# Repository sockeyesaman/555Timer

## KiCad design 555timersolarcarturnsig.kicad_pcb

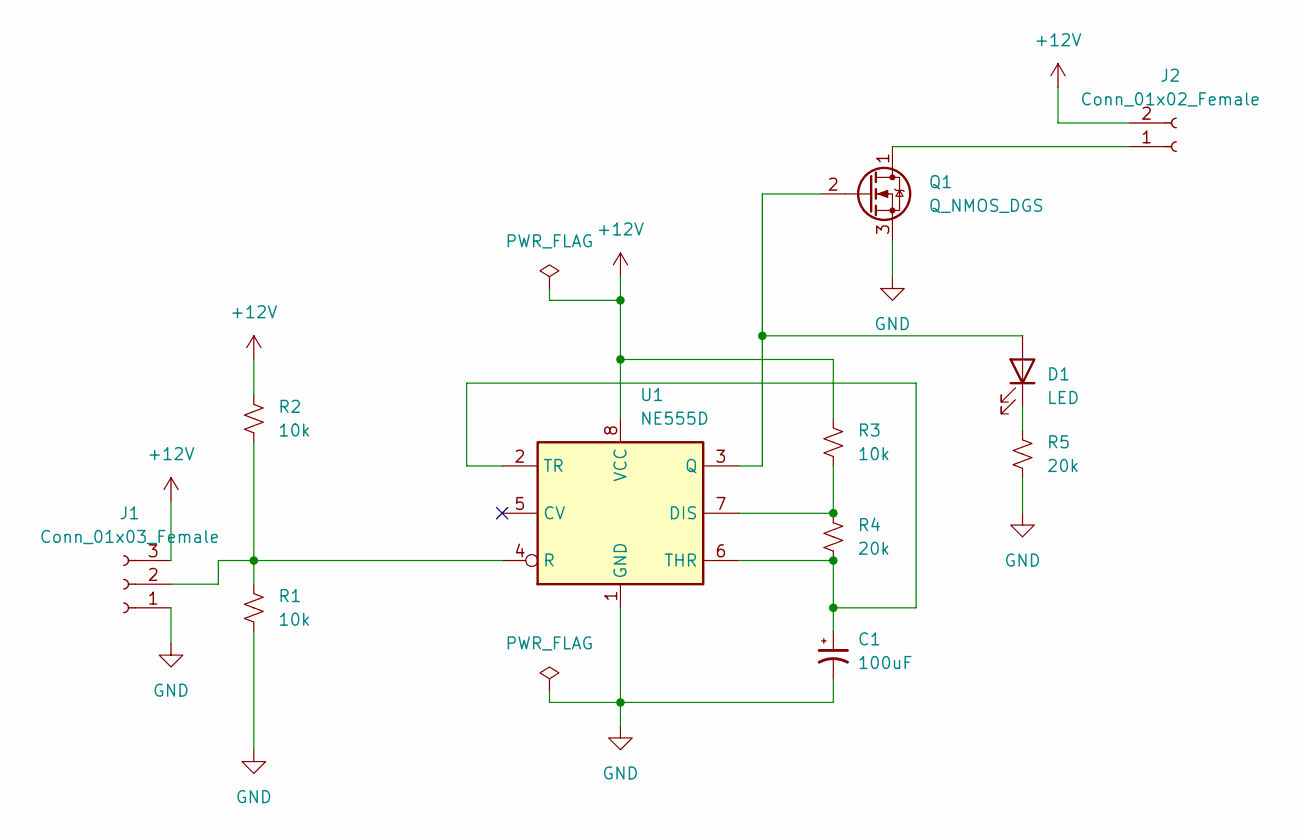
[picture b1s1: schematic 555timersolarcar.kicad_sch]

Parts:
C1: 100uF; CP_EIA-7360-38_Kemet-E_Pad2.25x4.25mm_HandSolder
D1: LED; LED_0805_2012Metric_Pad1.15x1.40mm_HandSolder
J1: Conn_01x03_Female; Molex_Micro-Fit_3.0_43650-0321_1x03_P3.00mm_Vertical
J2: Conn_01x02_Female; Molex_Micro-Fit_3.0_43650-0221_1x02_P3.00mm_Vertical
Q1: Q_NMOS_DGS; TO-252-2_TabPin1
R1, R2, R3: 10k; R_0805_2012Metric_Pad1.20x1.40mm_HandSolder
R4, R5: 20k; R_0805_2012Metric_Pad1.20x1.40mm_HandSolder
U1: NE555D; SOIC-8_3.9x4.9mm_P1.27mm

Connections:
+12V: J1.3, J2.2, R2.1, R3.1, U1.8 (VCC)
GND: C1.2, J1.1, Q1.3 (S), R1.2, R5.1, U1.1 (GND)
unnamed: D1.1 (K), R5.2
unnamed: D1.2 (A), Q1.2 (G), U1.3 (Q)
unnamed: J1.2, R1.1, R2.2, U1.4 (R)
unnamed: J2.1, Q1.1 (D)
unnamed: R3.2, R4.1, U1.7 (DIS)
unnamed: C1.1, R4.2, U1.2 (TR), U1.6 (THR)

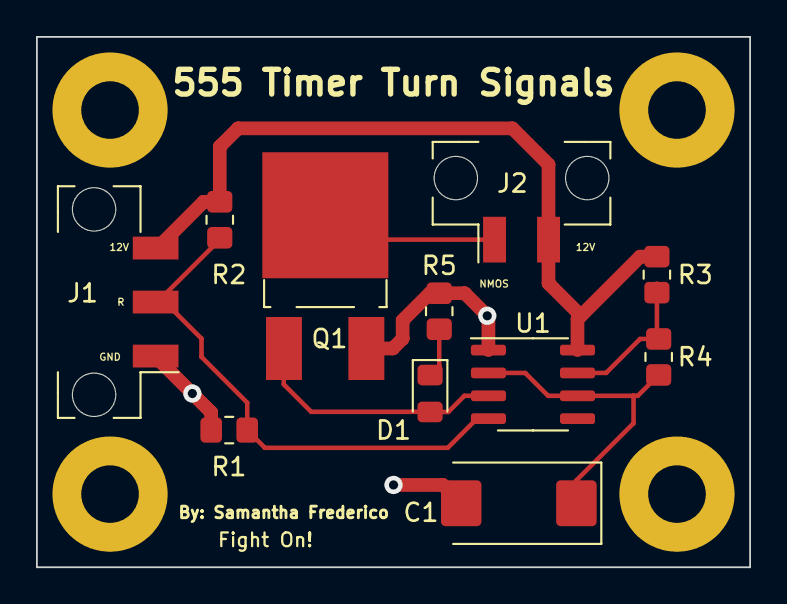
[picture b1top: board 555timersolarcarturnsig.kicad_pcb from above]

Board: 2 copper layers, 39.6 x 29.5 mm, 11 parts (0 on the bottom side), 8 nets.
